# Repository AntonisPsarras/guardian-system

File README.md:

# Guardian System

A local Home Assistant door system: RFID at two doors, a keypad-and-display
portal, and a porch lantern that does not advertise a camera.

**Start here:** [INSTALL.md](INSTALL.md) — from a fresh Home Assistant to a
working system. **Start with the print:** the lantern. No custom PCB; one
weekend if you already have a Tapo C110.

Maintainer: [AntonisPsarras](https://github.com/AntonisPsarras).

> Ready with documented caveats. Not a product, not an add-on, not supported.
> A burglar alarm that fails does so at the worst possible moment. Read the
> caveats below before you run it. MIT, **as is, without warranty**.

<table>
  <tr>
    <td align="center" valign="top" width="34%">
      
      <br /><strong>Door lantern</strong>
    </td>
    <td align="center" valign="top" width="33%">
      
      <br /><strong>Interior portal</strong>
    </td>
    <td align="center" valign="top" width="33%">
      
      <br /><strong>Doorbell</strong>
    </td>
  </tr>
</table>

Step-by-step assembly with more photographs is in
[`docs/documentation/`](docs/documentation/).

## Caveats

1. **No proven alarm without Wi-Fi.** The portal's offline siren compiles
   and has never been heard. Until you flash it and hear it, jamming
   2.4 GHz or stopping Home Assistant silences the house. Cutting power
   to the portal still does: authority is RAM-only.
2. **Printable as 3MF profiles plus generic STLs; Gerbers for a proto
   fab; not pick-and-place.** Print files live on MakerWorld,
   Printables, and Thingiverse. `PCBs/` has KiCad source plus
   Gerber+drill zips. There is no CPL. The door lamp has no PCB —
   commercial bulb + camera in a printed housing.
3. **The outdoor unit holds the card master key in cleartext flash until
   you opt into flash encryption.** That burn is irreversible; a first
   flash over OTA would brick the board. See INSTALL.md § Flash
   encryption. Use NTAG21x; MIFARE Classic is clonable.
4. **One Home Assistant account still works with zero extra setup.** A
   second account can be linked to a key. Tamper detection needs a
   portal reflash.

## What this is

Not application source code. It is the **config tree for a Home
Assistant instance**, plus firmware for two ESP32 devices:

| Piece | What it is |
|---|---|
| **Interior portal** | ESP32 at the main door: RC522 RFID, keypad, 240×135 ST7789 display, LED, door contact, lever IMU, DFPlayer for siren and chirps. |
| **Doorbell unit** | A second ESP32 outside: RFID reader and button. A key works from outside without the portal. |
| **Home Assistant** | Automations, scripts, and helper packages. All the actual logic. |
| **Frigate** | A separate NVR add-on for person detection, reaching Guardian over MQTT. |
| **Guardian panel** | A custom Home Assistant panel in one vanilla-JS ES module. No build step. |

There is no application build and no way to execute this locally. The
only way to run it is a real Home Assistant instance and real hardware.

## What it does

- **Two readers, one decision path.** Every scan dispatches through one
  script. Cloned cards are caught by a rolling counter; keys reported
  stolen sound the siren on the tap.
- **Passage windows.** A valid scan opens a timed grace period. Direction
  is classified from the lever IMU, reader intent, and the door swing.
- **Elevated mode** ("Super Surveillance"), on a switch or up to four
  schedules. An unauthenticated opening while elevated opens a timed
  challenge — card *and* master PIN — before the alarm.
- **Alerting per person.** Each key can link a phone. The alarm, a stolen
  card, and portal tamper are non-maskable.
- **Watchdogs** on the portal, the doorbell, and the Frigate detection
  channel.
- **A door lamp** switched from measured camera luminance, with a
  sun-elevation fallback.

## Print files

Meshes are not in this tree. Each listing is a Bambu Studio `.3mf` plus a
generic STL zip for slicers that are not Bambu. Start with the lantern.

[MakerWorld collection](https://makerworld.com/en/collections/36079462-guardian-system)
· [Printables collection](https://www.printables.com/@AntoniJuveni_3576373/collections/3780824)
(account `@AntoniJuveni_3576373`; the project handle is AntonisPsarras)

| Device | Profile | MakerWorld | Printables |
|---|---|---|---|
| Door lantern (Tapo C110 + L530E) | `Lamp-Final.3mf` | [listing](https://makerworld.com/en/models/3347455-guardian-door-lamp-housing-tapo-c110-lantern) | [listing](https://www.printables.com/model/1853736-guardian-door-lantern-tapo-c110-camera-l530e-hidde) |
| Interior portal | `Internal-Portal-Final.3mf` | [listing](https://makerworld.com/en/models/3347482-guardian-interior-portal-keypad-and-display) | [listing](https://www.printables.com/model/1853748-guardian-interior-portal-esp32-s3-keypad-rfid-disp) |
| Doorbell | `Doorbell-Final.3mf` | [listing](https://makerworld.com/en/models/3347498-guardian-outdoor-doorbell-housing-esp32-c6) | [listing](https://www.printables.com/model/1853742-guardian-outdoor-doorbell-housing-esp32-c6) |

## Documentation

| File | Read it for |
|---|---|
| [`INSTALL.md`](INSTALL.md) | Day-one path: prerequisites, file placement, restart, setup wizard, what leaves your network. |
| [`docs/`](docs/) | Hardware index: assembly, printable PDFs, parts checklist, DFPlayer tracks. |
| [`docs/documentation/`](docs/documentation/) | Assembly photographs, soldering order, and a printable PDF per device. |
| [`docs/bom.md`](docs/bom.md) | One-page parts checklist. Not a pick-and-place file. |
| [`PCBs/`](PCBs/) | Two KiCad 10 projects and Gerber+drill zips. |
| [`3D-Models/`](3D-Models/) | Where the print files live (MakerWorld / Printables / Thingiverse). This tree does not ship meshes. |
| [`SECURITY.md`](SECURITY.md) | How to report a problem, and what not to paste into an issue. |
| [`CONTRIBUTING.md`](CONTRIBUTING.md) | Preflight, selftest, and how to propose a change. |
| [`DEPLOY.md`](DEPLOY.md) | Maintainer changelog **and** manual test plan. |
| [`docs/maintainers/`](docs/maintainers/) | Audit, panel design, contributor onboarding. |

## Checking a change

There is exactly one automated check, and it is static:

```bash
python tools/guardian-preflight.py
```

It validates that every YAML file parses, that version literals agree,
that script references resolve, that automation ids are unique, that no
secret placeholder survives, that nothing under `www/guardian-ui/`
reaches an external host, and that nothing can quietly cancel an alert.
It makes no network call and reads no credential value.

And one test for that check:

```bash
python tools/guardian-selftest-preflight.py
```

**It does not test behaviour.** Nothing here fires an alarm. For that,
use Home Assistant's *Check configuration* and the numbered steps in
`DEPLOY.md`.

## Security model

Stated plainly, because the parts that are careful could be mistaken for
parts that are enforced.

- **A Home Assistant login is the outer authorization boundary.** The
  panel is `require_admin: false` so a non-administrator can use Keys
  and Notifications. Home Assistant still does not restrict which
  services a non-admin may call from Developer Tools. See
  [`docs/maintainers/GUARDIAN_UI.md`](docs/maintainers/GUARDIAN_UI.md)
  § *Security boundaries*.
- **The siren does not work without Wi-Fi and Home Assistant** on any
  device that has not been flashed with current firmware and then heard.
  The networked siren is an MP3 on the portal's DFPlayer. Jam 2.4 GHz,
  cut power to the access point, or take Home Assistant down and there
  is no *proven* alarm.
- **The card master key is in cleartext flash** on a unit mounted
  outside the door until you opt into flash encryption.
- **MIFARE Classic cards are clonable.** NTAG21x with a password is the
  medium that is actually strong here.
- **Rotating the master key destroys every enrolled card**, both types,
  with no way back.
- **The master PIN hash is weak by construction**: unsalted SHA-256 of
  4–6 digits. It is a second factor at a door, not a secret.
- **Dismissing a live alarm needs no factor.** Any phone holding the
  alarm push can silence it. That is deliberate.
- **Every alarm notification leaves your network** via Apple or Google.
  Do not port-forward Home Assistant. See `INSTALL.md` §10.
- Credentials live in `esphome/secrets.yaml` (gitignored, generated by
  `tools/guardian-gen-secrets.py`), Frigate add-on environment
  variables, and the master PIN.

## Where it actually stands

**Works, in daily use in one household:** RFID entry at both readers,
presence per key, passage windows and direction classification, the
MFA/challenge flow, enrollment, per-person alert routing, the lamp, the
panel, the offline watchdogs.

**Known gaps, deliberately not hidden:**

- Print files are 3MF profiles plus generic STL zips on MakerWorld /
  Printables / Thingiverse; Gerbers are in `PCBs/`. Not pick-and-place.
- Card-crypto and torn-rotate fixes are in the tree and **unverified
  against a real card** since those passes.
- The offline local siren compiles and **has never been heard**.
- Tamper detection needs a portal reflash.
- The alarm path is unverified on hardware since the last several
  passes. `INSTALL.md` §9 remains the proof.
- Frigate integrates over raw MQTT, not the native integration.
- Single-household provenance. This has only ever run on one
  installation.

Early private git history contained a household LAN address and a camera
RTSP URL. This public repository was seeded from a cleaned tree; that
log is not here. If those credentials were ever live, rotate them.

## Support

This is unpaid and unsupported. If you still want to buy coffee:

- GitHub Sponsors on this repository (see `.github/FUNDING.yml`)
- A Ko-fi link will be added here when that account exists

[`docs/bom.md`](docs/bom.md) has no affiliate tags. If any appear later,
they will be disclosed in that file.

## License

[MIT](LICENSE). This is a burglar alarm provided **as is, without
warranty of any kind**. If you run it, you own the consequences of it
failing.

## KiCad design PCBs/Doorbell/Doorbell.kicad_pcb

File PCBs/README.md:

# PCBs

Two through-hole boards live here. Send a fab the Gerber zip for the board you
want made; solder the modules yourself. There is no lamp PCB — that housing
takes a commercial bulb and a commercial camera.

Firmware is the pin authority. The schematics use generic connectors and
auto-named nets, not GPIO labels. Derive the pinout from
[`esphome/portal-unit.yaml`](../esphome/portal-unit.yaml) and
[`esphome/doorbell-unit.yaml`](../esphome/doorbell-unit.yaml), or from the table
in [`INSTALL.md`](../INSTALL.md) §1.

Assembly photographs and soldering order:
[`docs/documentation/interior-portal/`](../docs/documentation/interior-portal/)
and [`docs/documentation/doorbell/`](../docs/documentation/doorbell/).

## What to send a fab

Each zip is a complete 2-layer Gerber + drill set: copper, soldermask, paste,
silkscreen, edge cuts, plated and non-plated drill, and the job file.

| Board | KiCad project | Send this zip |
|---|---|---|
| Interior portal (ESP32-S3) | [`Interior-Portal/`](Interior-Portal/) | [`Interior-Portal/Interior-Portal-Gerbers.zip`](Interior-Portal/Interior-Portal-Gerbers.zip) |
| Doorbell (XIAO ESP32-C6) | [`Doorbell/`](Doorbell/) | [`Doorbell/Doorbell-Gerbers.zip`](Doorbell/Doorbell-Gerbers.zip) |
| Door lamp + camera | — | None. Commercial parts in a printed housing. |

Designed in **KiCad 10.0**. These are **THT proto boards**, not an SMT
assembly job. There is no pick-and-place / CPL file, and none is needed:
a board house fabricates the bare PCB; you populate headers, resistors,
and the polarised capacitor by hand.

**Upload the zip. Do not request SMT / JLCPCB assembly.**

### Fab card

| | Interior portal | Doorbell |
|---|---|---|
| Outline | 50.8 × 124.5 mm | 48.3 × 35.6 mm |
| Layers | 2 | 2 |
| Thickness | 1.6 mm | 1.6 mm |
| Copper | 1 oz | 1 oz |
| Finish | HASL | HASL |
| Soldermask / silk | green / white (fab default is fine) | green / white |
| Schematic (no KiCad needed) | [`Interior-Portal-schematic.pdf`](Interior-Portal/Interior-Portal-schematic.pdf) | [`Doorbell-schematic.pdf`](Doorbell/Doorbell-schematic.pdf) |
| Assembly photos | [interior-portal](../docs/documentation/interior-portal/images/03.png) | [doorbell](../docs/documentation/doorbell/images/03.png) |

Boards, prints, and firmware in this repository are [MIT](../LICENSE).

## Interior portal BOM (placed passives)

Values match the KiCad instances and the silkscreen.

| Qty | Ref | Value | Footprint | Notes |
|---|---|---|---|---|
| 3 | R1–R3 | 220 Ω | Axial THT (DIN0207) | Status LED |
| 2 | R4–R5 | 1 kΩ | Axial THT (DIN0207) | |
| 1 | C1 | 1000 µF 10 V | Radial D10.0 mm, P5.00 mm | Polarised. Match the `+` mark on the board. |

Plus: ESP32-S3 DevKit (firmware `flash_size: 8MB`), MFRC522, MPU6050, DFPlayer
Mini, 4×3 keypad, 240×135 ST7789 IPS, reed switch, speaker, headers as in the
assembly doc.

## Doorbell BOM (placed passives)

| Qty | Ref | Value | Footprint | Notes |
|---|---|---|---|---|
| 3 | R1–R3 | 220 Ω | Axial THT (DIN0207) | Optional RGB LED |
| 1 | R4 | 10 kΩ | Axial THT (DIN0207) | Push button. Firmware also enables the ESP32 internal pull-up, so the button still works with no external resistor. |

Plus: Seeed Studio XIAO ESP32-C6, MFRC522, 12 mm momentary button, optional
common-anode 5 mm RGB LED, headers as in the assembly doc.

The RFID header is labelled **RFID1**.

## What is still not in these files

- No GPIO names on the nets (`Net-(XIAO_LEFT1-Pin_1)`, not `SDA`).
- Unused MCU pads are unconnected on purpose.
- No IPC-2581, ODB++, or CPL — those are for SMT / contract manufacturing.

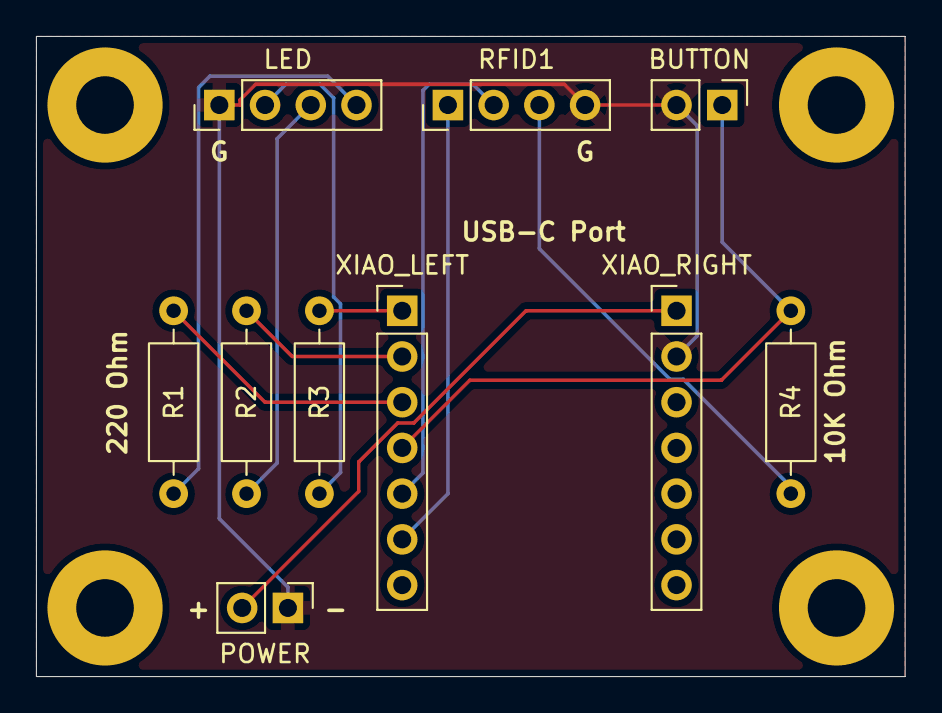
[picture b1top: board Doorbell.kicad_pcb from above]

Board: 2 copper layers, 48.3 x 35.6 mm, 14 parts (0 on the bottom side), 12 nets.

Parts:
BUTTON: Conn_01x02_Pin; PinHeader_1x02_P2.54mm_Vertical
H1, H2, H3, H4: MountingHole; MountingHole_3.2mm_M3_Pad
LED: Conn_01x04_Pin; PinHeader_1x04_P2.54mm_Vertical
POWER: Conn_01x02_Pin; PinHeader_1x02_P2.54mm_Vertical
R1, R2, R3: 220; R_Axial_DIN0207_L6.3mm_D2.5mm_P10.16mm_Horizontal
R4: 10k Ohm; R_Axial_DIN0207_L6.3mm_D2.5mm_P10.16mm_Horizontal
RFID1: Conn_01x04_Pin; PinHeader_1x04_P2.54mm_Vertical
XIAO_LEFT: Conn_01x07_Pin; PinHeader_1x07_P2.54mm_Vertical
XIAO_RIGHT: Conn_01x07_Pin; PinHeader_1x07_P2.54mm_Vertical

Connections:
+5V: POWER.2, XIAO_RIGHT.1
GND: BUTTON.2, LED.1, POWER.1, RFID1.4, XIAO_RIGHT.2
unnamed: BUTTON.1, R4.2, XIAO_LEFT.4
unnamed: LED.2, R3.1
unnamed: LED.3, R2.1
unnamed: LED.4, R1.1
unnamed: RFID1.1, XIAO_LEFT.6
unnamed: RFID1.2, XIAO_LEFT.5
unnamed: R4.1, RFID1.3
unnamed: R3.2, XIAO_LEFT.1
unnamed: R2.2, XIAO_LEFT.2
unnamed: R1.2, XIAO_LEFT.3

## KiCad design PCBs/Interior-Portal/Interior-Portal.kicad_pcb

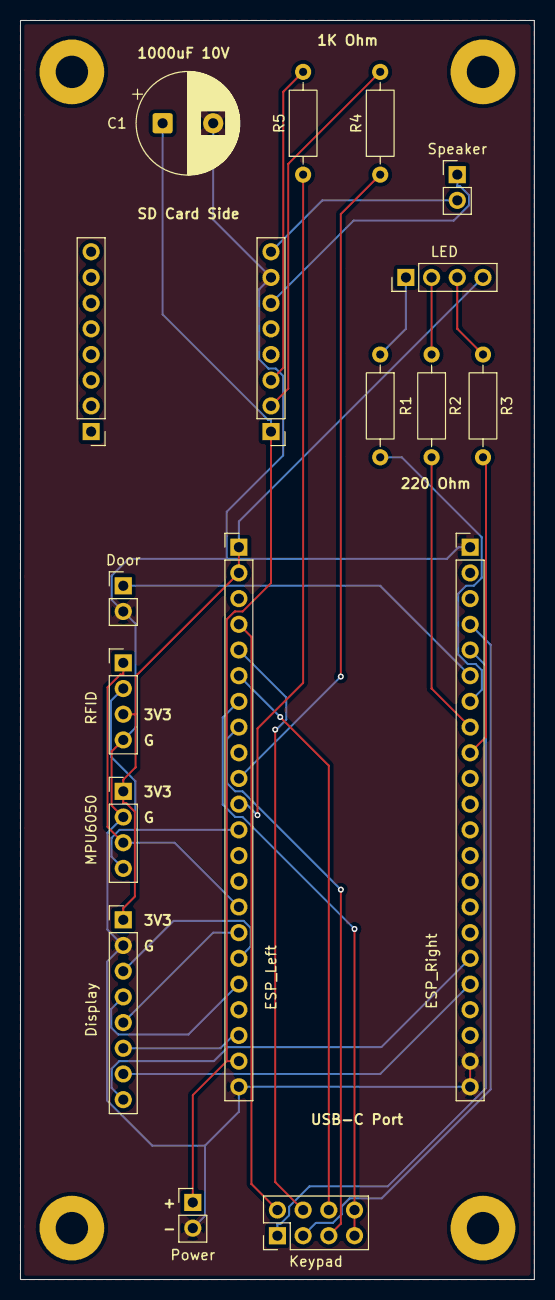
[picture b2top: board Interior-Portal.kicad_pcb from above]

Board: 2 copper layers, 50.8 x 124.5 mm, 22 parts (0 on the bottom side), 31 nets.

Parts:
C1: 1000uF 10V; CP_Radial_D10.0mm_P5.00mm
DFPlayer_Left1: Conn_01x08_Pin; PinHeader_1x08_P2.54mm_Vertical
DFPlayer_Right1: Conn_01x08_Pin; PinHeader_1x08_P2.54mm_Vertical
Display: Conn_01x08_Pin; PinHeader_1x08_P2.54mm_Vertical
Door: Conn_01x02_Pin; PinHeader_1x02_P2.54mm_Vertical
ESP_Left: Conn_01x22_Pin; PinHeader_1x22_P2.54mm_Vertical
ESP_Right: Conn_01x22_Pin; PinHeader_1x22_P2.54mm_Vertical
H1, H2, H3, H4: MountingHole; MountingHole_3.2mm_M3_Pad
Keypad: Conn_02x04_Odd_Even; PinHeader_2x04_P2.54mm_Vertical
LED: Conn_01x04_Pin; PinHeader_1x04_P2.54mm_Vertical
MPU6050: Conn_01x04_Pin; PinHeader_1x04_P2.54mm_Vertical
Power: Conn_01x02_Pin; PinHeader_1x02_P2.54mm_Vertical
R1, R2, R3: 220; R_Axial_DIN0207_L6.3mm_D2.5mm_P10.16mm_Horizontal
R4, R5: 1K; R_Axial_DIN0207_L6.3mm_D2.5mm_P10.16mm_Horizontal
RFID: Conn_01x04_Pin; PinHeader_1x04_P2.54mm_Vertical
Speaker: Conn_01x02_Pin; PinHeader_1x02_P2.54mm_Vertical

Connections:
+3V3: Display.1, ESP_Left.1, ESP_Left.2, LED.4, MPU6050.1, RFID.3
+5V: C1.1, DFPlayer_Left1.1, ESP_Left.21, Power.1
GND: C1.2, DFPlayer_Left1.7, Display.2, Door.2, ESP_Left.22, ESP_Right.1, ESP_Right.21, ESP_Right.22, MPU6050.2, Power.2, RFID.4
unnamed: DFPlayer_Left1.2, R4.2
unnamed: DFPlayer_Left1.3, R5.2
unnamed: DFPlayer_Left1.6, Speaker.1
unnamed: DFPlayer_Left1.8, Speaker.2
unnamed: Display.3, ESP_Left.17
unnamed: Display.4, ESP_Left.18
unnamed: Display.5, ESP_Left.16
unnamed: Display.6, ESP_Left.20
unnamed: Display.7, ESP_Right.18
unnamed: Display.8, ESP_Right.17
unnamed: Door.1, ESP_Right.6
unnamed: ESP_Left.4, Keypad.2
unnamed: ESP_Left.5, Keypad.4
unnamed: ESP_Left.6, Keypad.6
unnamed: ESP_Left.7, Keypad.7, Keypad.8
unnamed: ESP_Left.8, Keypad.5
unnamed: ESP_Left.10, R4.1
unnamed: ESP_Left.11, R5.1
unnamed: ESP_Left.12, MPU6050.4, RFID.2
unnamed: ESP_Left.15, MPU6050.3, RFID.1
unnamed: ESP_Right.4, Keypad.3
unnamed: ESP_Right.5, Keypad.1
unnamed: ESP_Right.7, R1.2
unnamed: ESP_Right.8, R2.2
unnamed: ESP_Right.9, R3.2
unnamed: LED.1, R1.1
unnamed: LED.2, R2.1
unnamed: LED.3, R3.1
